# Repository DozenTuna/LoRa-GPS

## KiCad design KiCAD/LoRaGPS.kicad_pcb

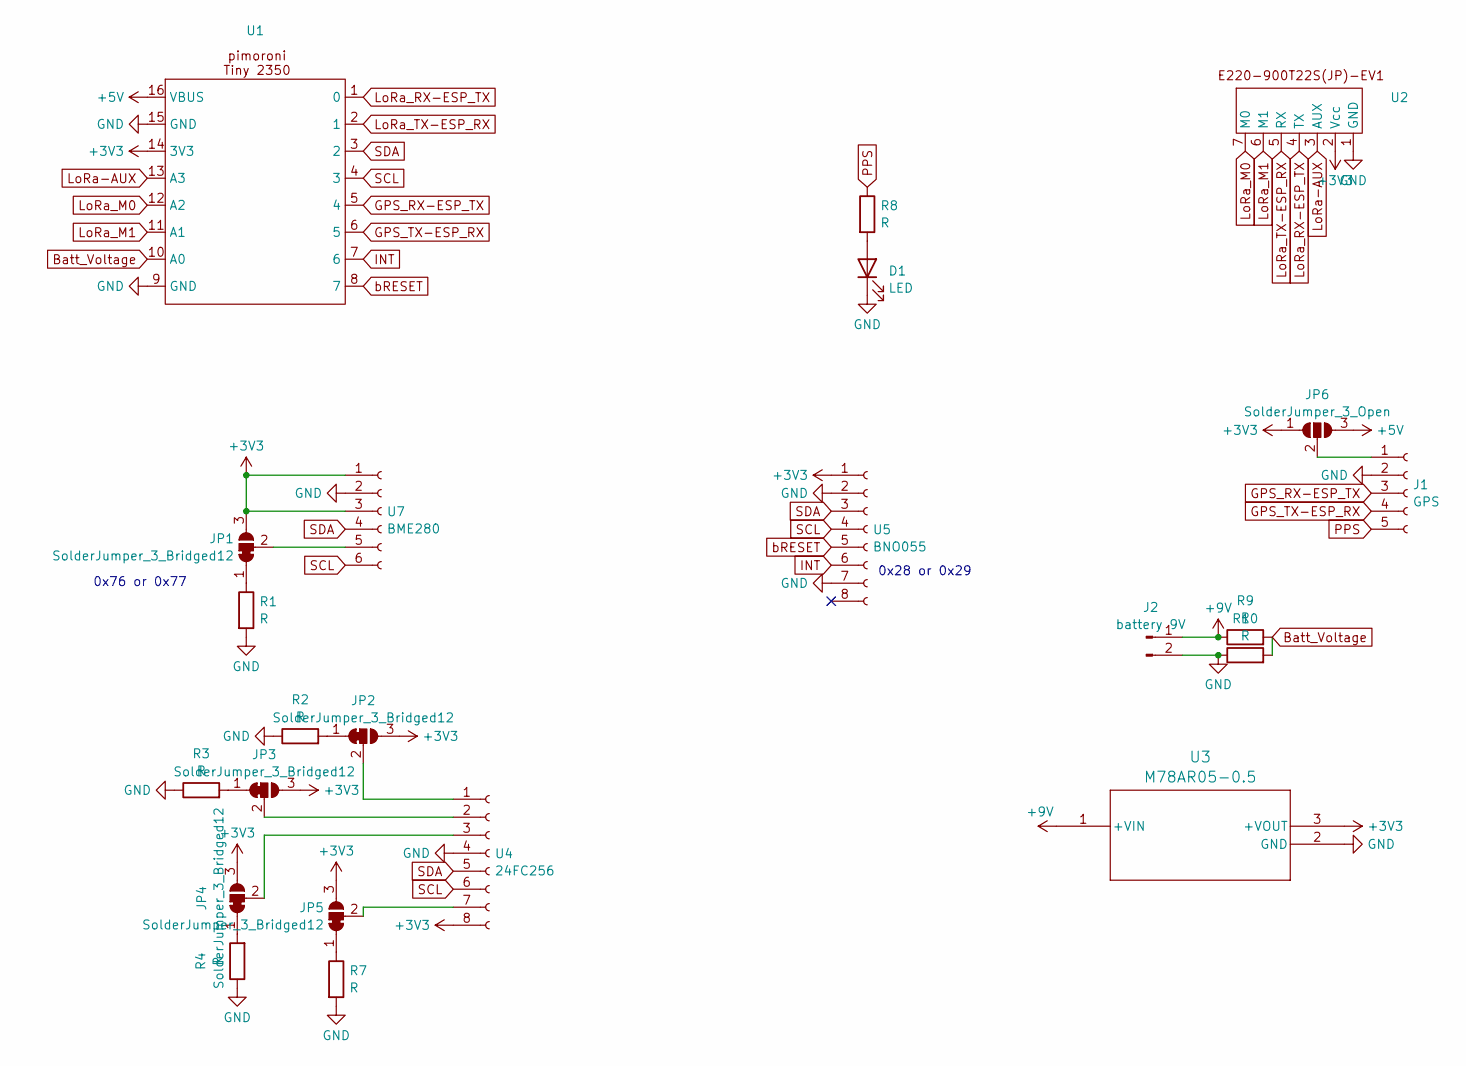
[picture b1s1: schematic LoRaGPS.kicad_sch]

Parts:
D1: LED; D_0603_1608Metric_Pad1.05x0.95mm_HandSolder
J1: GPS; JST_XH_S5B-XH-A_1x05_P2.50mm_Horizontal
J2: battery 9V; JST_XH_S2B-XH-A_1x02_P2.50mm_Horizontal
JP1, JP2, JP3, JP4, JP5: SolderJumper_3_Bridged12; SolderJumper-3_P1.3mm_Bridged12_RoundedPad1.0x1.5mm
JP6: SolderJumper_3_Open; SolderJumper-3_P1.3mm_Open_Pad1.0x1.5mm
R1, R2, R3, R4, R7, R8, R9, R10: R; R_0603_1608Metric_Pad0.98x0.95mm_HandSolder
U1: Tiny 2350
U2: E220-900T22S(JP)-EV1
U3: M78AR05-0.5; SIP3_M78AR-0.5_MIN
U4: 24FC256; DIP-8_W7.62mm
U5: BNO055; AE-BNO055-BO
U7: BME280; AE-BME280

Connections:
+3V3: JP1.3 (B), JP2.3 (B), JP3.3 (B), JP4.3 (B), JP5.3 (B), JP6.1 (A), U1.14 (3V3), U2.2 (Vcc), U3.3 (+VOUT), U4.8, U5.1, U7.1, U7.3
+5V: JP6.3 (B), U1.16 (VBUS)
+9V: J2.1, R9.1, U3.1 (+VIN)
Batt_Voltage: R9.2, R10.2, U1.10 (A0)
GND: D1.1 (K), J1.2, J2.2, R1.2, R2.1, R3.1, R4.1, R7.2, R10.1, U1.9 (GND), U1.15 (GND), U2.1 (GND), U3.2 (GND), U4.4, U5.2, U5.7, U7.2
GPS_RX-ESP_TX: J1.3, U1.5 (4)
GPS_TX-ESP_RX: J1.4, U1.6 (5)
INT: U1.7 (6), U5.6
LoRa-AUX: U1.13 (A3), U2.3 (AUX)
LoRa_M0: U1.12 (A2), U2.7 (M0)
LoRa_M1: U1.11 (A1), U2.6 (M1)
LoRa_RX-ESP_TX: U1.1 (0), U2.4 (TX)
LoRa_TX-ESP_RX: U1.2 (1), U2.5 (RX)
unnamed: D1.2 (A), R8.2
unnamed: J1.1, JP6.2 (C)
unnamed: JP1.1 (A), R1.1
unnamed: JP1.2 (C), U7.5
unnamed: JP2.1 (A), R2.2
unnamed: JP2.2 (C), U4.1
unnamed: JP3.1 (A), R3.2
unnamed: JP3.2 (C), U4.2
unnamed: JP4.1 (A), R4.2
unnamed: JP4.2 (C), U4.3
unnamed: JP5.1 (A), R7.1
unnamed: JP5.2 (C), U4.7
PPS: J1.5, R8.1
SCL: U1.4 (3), U4.6, U5.4, U7.6
SDA: U1.3 (2), U4.5, U5.3, U7.4
bRESET: U1.8 (7), U5.5

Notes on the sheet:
0x76 or 0x77
0x28 or 0x29

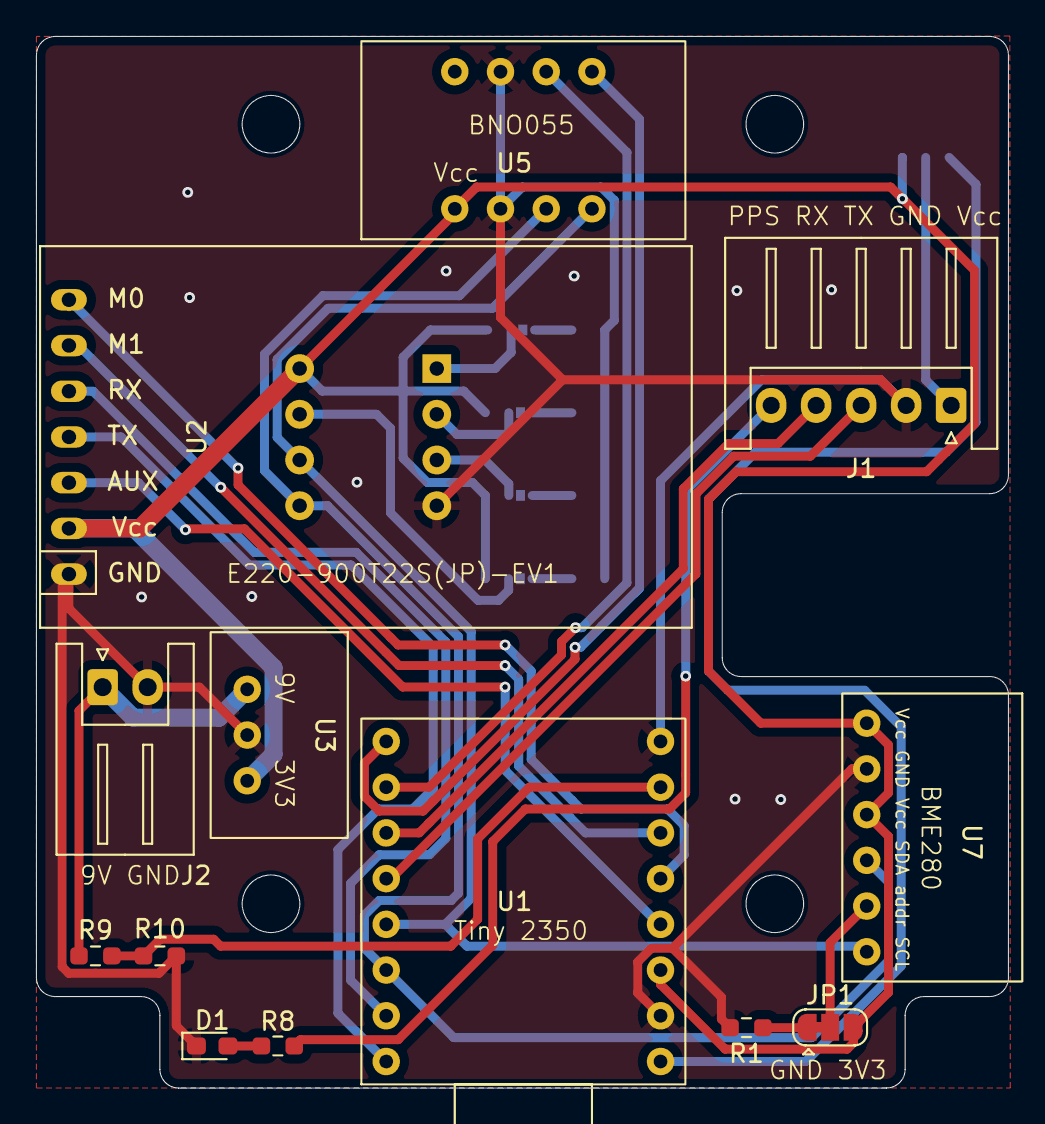
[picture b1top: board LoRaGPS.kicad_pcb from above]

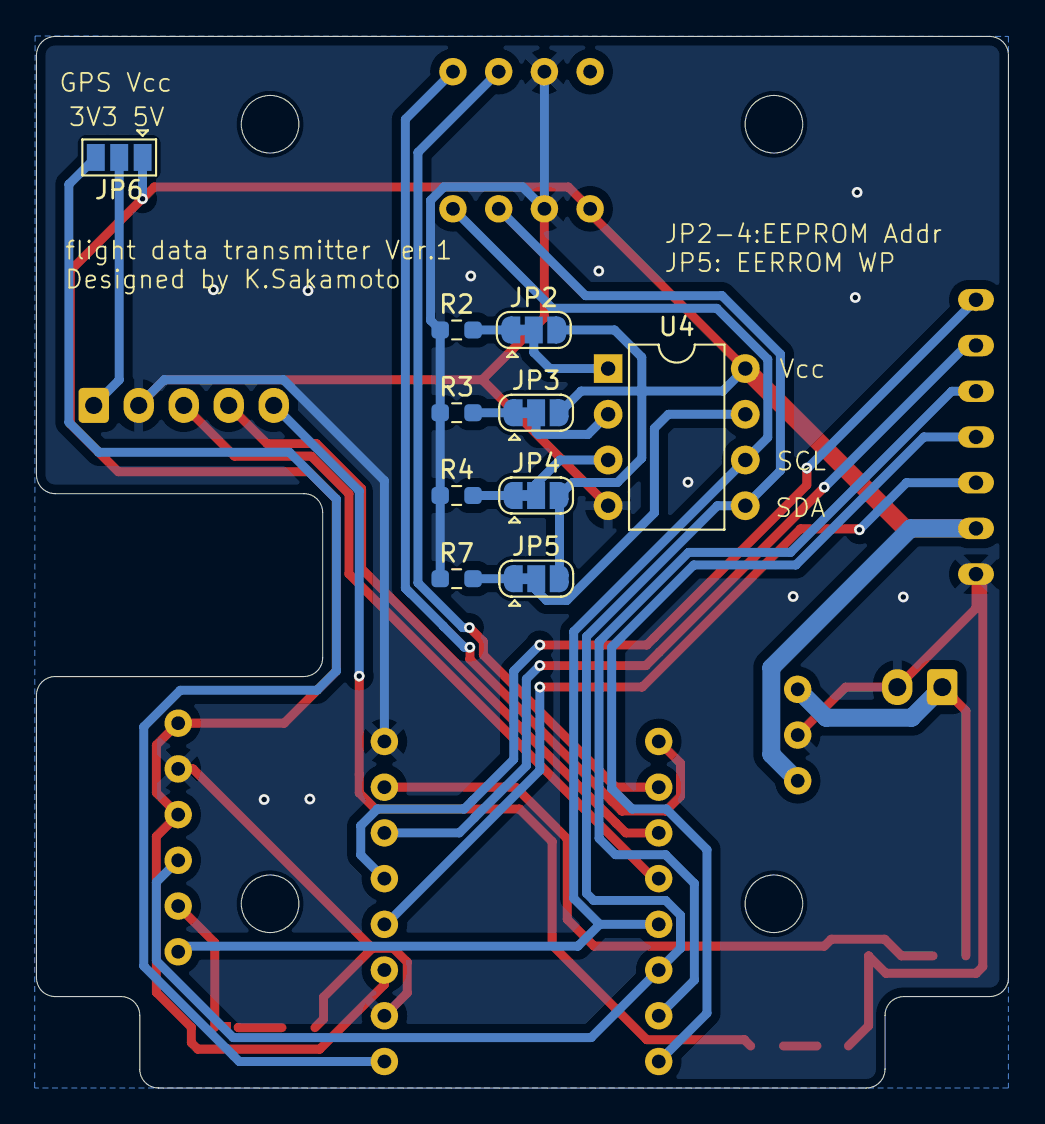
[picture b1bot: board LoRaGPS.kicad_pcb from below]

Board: 2 copper layers, 54.0 x 58.4 mm, 23 parts (10 on the bottom side), 29 nets.

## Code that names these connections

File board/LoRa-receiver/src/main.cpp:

#include <Arduino.h>
#include <Wire.h>

#define LED_R 18 //active low
#define LED_G 19 //active low
#define LED_B 20 //active low

#define LoRa_RxPin 1
#define LoRa_TxPin 0
#define GPS_RxPin 5
#define GPS_TxPin 4
#define Sensor_SDA 2
#define Sensor_SCL 3
#define SerialLoRa Serial1
#define SerialGPS Serial2
#define WireSensor Wire1
#define WireQT Wire

#define LoRa_AUX 29
#define LoRa_M0 28
#define LoRa_M1 27
#define Batt_Voltage 26
#define Button 23 //active low

void setup() {
  // put your setup code here, to run once:
  Serial.begin(115200);
  delay(1000);
  Serial.println("Hello World");
  SerialLoRa.setRX(LoRa_RxPin);
  SerialLoRa.setTX(LoRa_TxPin);
  SerialLoRa.begin(9600);
  SerialGPS.setRX(GPS_RxPin);
  SerialGPS.setTX(GPS_TxPin);
  SerialGPS.begin(9600);
  WireSensor.setSDA(Sensor_SDA);
  WireSensor.setSCL(Sensor_SCL);
  WireSensor.begin();
  WireQT.setSDA(12);
  WireQT.setSCL(13);
  WireQT.begin();
  pinMode(LED_BUILTIN, OUTPUT);
}

void loop() {
  // put your main code here, to run repeatedly:
  digitalWrite(LED_BUILTIN, HIGH);
  delay(1000);
  digitalWrite(LED_BUILTIN, LOW);
  delay(1000);
  Serial.println("loop");
}

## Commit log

2024-12-14 create initial source code of transmitter
2024-12-14 create initial source code of LoRa receiver
2024-12-14 create gitignore
2024-12-15 add reference on schematic
2024-12-15 add description on pin definition
2024-12-16 update gitignore
2024-12-16 update gitignore (datasheets)
2024-12-26 rename folder
2024-12-26 optimize same name folder
2024-12-27 create code to read env sensor
2024-12-27 update gitignore and file structure
2024-12-27 create initial code to get attitude
2024-12-27 change file structure and update gitignore
2024-12-30 trivial
2024-12-30 change file structure
2024-12-31 LoRa test done!
2024-12-31 create LoRa library file
2025-01-01 success to get gps position datas
2025-01-01 create EEPROM read / write codes
